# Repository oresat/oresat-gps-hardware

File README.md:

# oresat-gps-hardware 

## Overview

This is the repo for our OreSat GPS Card. For software, see the [oresat-gps-software](https://github.com/oresat/oresat-gps-software) repo.

The card has two GPS receivers on it:

* A [**SkyTraq Orion-B16** GNSS module](https://navspark.mybigcommerce.com/12mm-x-16mm-gnss-receiver-module-for-leo-applications/), a GNSS receiver module meant for university CubeSat use.
* An [Analog Devices MAX2771 SDR GNSS receiver IC](https://www.analog.com/en/products/max2771.html) that is read by the [Octavo OSD335x-SM processor's](https://octavosystems.com/octavo_products/osd335x-sm/) PRU and then parsed using the [GNSS-SDR project](https://gnss-sdr.org/) software.

## Status

TRL 6-7 ish. Flown, but not yet demonstrated to work in space.

* v1.1: Assembled, electrical and software test out, Orion not yet locked and demonstrated to work. MAX not yet tested.
* v1.0: Works: SkyTraq confirmed locked on ground. SDR datastream captured, and processed, but this software seems to be lost to the sands of time? Flown on OreSat0 but never turned on due to comms issues with OreSat0.

## License

All materials in this repo are copyright Portland State Aerospace Society and are licensed under the CERN Open Hardware Licence Version 2 -
Strongly Reciprocal (CERN-OHL-S v2), or any later version. A copy of the license is located in [here](LICENSE.md).

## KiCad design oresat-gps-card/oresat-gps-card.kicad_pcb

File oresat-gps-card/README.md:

---
title: "**OreSat GPS Card**"
subtitle: |
  **Fabrication and Assembly Information**\
  For build TIME-STAMP
fontsize: 10pt
geometry:
  - margin=0.5in
toc: true
toc-depth: 2
colorlinks: true
urlcolor: blue
---

\newpage

# About this Board

## Board Description

The OreSat GPS Card provides two GPS receivers for the OreSat bus:

1. The SkyTraq Orion B16 which is a COTS GPS receiver capable of lock while in orbit.
2. The MAX2769 SDR GPS receiver. This hardware is for a future SDR capability we'd
like to have, and might one day replace the much more expensive COTS receiver.

## Documentation Links

- GPS hardware Git repository: <https://github.com/oresat/oresat-gps-hardware>
- GPS software Git reposity: <https://github.com/oresat/oresat-gps-software>
- **TODO:** GPS Design Notes + Design Review Notes

## Documentation Files

| Filename                        | Notes                                    |
| ------------------------------- | ---------------------------------------- |
| README.pdf                      | This README file                         |
| PROJECT-NAME-outline.dxf        | Board outline (with holes) in DXF format |
| PROJECT-NAME-pcba.step          | 3D model of PCBA (with components)       |
| PROJECT-NAME-render-bot.jpg     | Render of the top of the 3D model        |
| PROJECT-NAME-render-bot.jpg     | Render of the bottom of the 3D model     |
| PROJECT-NAME-schematic.pdf      | PDF of board schematics                  |

## Contact Information

- Website: <https://www.oresat.org/>
- Email: <oresat@pdx.edu>
- Instagram: @pdxaerospace

## Board Renders

{width=50%}
{width=50%}

\newpage

# Printed Circuit Board (PCB) Fabrication Information

## Board Info

- 4 layer board
- Bounding box is 99.8 x 94.6 mm (3.93 x 3.72 in)
- Board thickness is 1.59 mm (0.063 inch)
- **Important:** See Materials and Stack Up sections below

## Board Requirements

- Design Rules
    - Minimum Trace / Space design rules
       - Outer layers: 0.127 mm (5.0 mil) / 0.127 mm (5.0 mil)
       - Inner layers: 0.127 mm (5.0 mil) / 0.127 mm (5.0 mil)
    - Outer dimension router tolerance: +/- 0.254 mm (10.0 mil)
    - Hole placement tolerance: +/- 0.075 mm (3.0 mil)
    - Inner tab routed slot tolerance: +/- 0.254 mm (10.0 mil)
- Drills
   - Drill Positional Tolerance: 0.051 mm (2.0 mil)
   - Drill Size tolerance: +/- 0.064 mm (2.5 mil)
- Plated/Un-plated holes
  - There are 6 un-plated (NPT) holes
  - There are 1477 plated through (PTH) holes
  - PTH minimum diameter: 0.254 mm (10 mil)
  - PTH minimum annulus: 0.102 mm (4 mil) radius
- Outline/Routing
  - Requires a 1.0 mm or smaller diameter routing bit
- Slots
  - There are no slots.
- Cutouts
  - There are no cutouts
- There are 3 fiducials on the top layer.
- Panel tabs ("mouse bites")
   - Card edges must be smooth; no mouse bites or other intrusions into the card outline.
   - If external mouse bites are required, minimize and customer will remove by hand before assembly.
- If not otherwise specified, build to IPC 6012 Class 2 or better.

## Materials

- Controlled impedance
   - The stackup is critical for the performance of high speed signals on this board.
   - As long as the stackup is controlled, the board is not considered controlled impedance.
- Isola FR408HR or material with equivalent Dk.
- Board Surface treatment should be ENIG, althogh immersion Silver is acceptable.
- White silkscreen on top and bottom surface
- Taiyo PSR-4000 or equivalent soldermask on top and bottom, no requirements for color.

## Stack Up

| Layer         | Thickness           | Notes                                        |
|---------------|---------------------|----------------------------------------------|
| Top Copper    | 0.043 mm /  1.7 mil |  Layer 1 foil, 1 oz Cu after plating         |
| prepreg       | 0.200 mm /  7.9 mil |  Prepreg - Isola FR408HR 2113                |
| Layer 2       | 0.018 mm /  0.7 mil |  Layer 2 foil, 0.5 oz Cu                     |
| Core          | 0.991 mm /   39 mil |  Core Isola FR408HR                          |
| Layer 3       | 0.018 mm /  0.7 mil |  Layer 3 foil, 0.5 oz Cu                     |
| prepreg       | 0.200 mm /  7.9 mil |  Prepreg - Isola FR408HR 2113                |
| Bottom Copper | 0.043 mm /  1.7 mil |  Layer 4 foil, 1 oz copper after plating     |
| **Total Stackup** | **1.588 mm / 62.5 mil** |                                      |

## Array / Panel Information

- Coordinate with Contract Manufacturer (CM) for optimal size of this panel.
- If no feedback from CM, then produce single boards (no panel).

## Fabrication Files

### IPC-2581 File

| Filename                 | Notes                                   |
| ------------------------ | --------------------------------------- |
| PROJECT-NAME-ipc2581.xml | IPC-2581 board information file         |

### Legacy PCB Files

| Filename                      | Notes                                         |
| ------------------------------| --------------------------------------------- |
| PROJECT-NAME-Edge_Cuts.gbr    | RS274X file for the dimension (outline) layer |
| PROJECT-NAME-F_Silkscreen.gbr | RS274X file for the top silkscreen            |
| PROJECT-NAME-F_Mask.gbr       | RS274X file for the top soldermask            |
| PROJECT-NAME-F_Cu.gbr         | RS274X file for the top copper layer          |
| PROJECT-NAME-In1_Cu.gbr       | RS274X file for the layer 2 copper            |
| PROJECT-NAME-In2_Cu.gbr       | RS274X file for the layer 3 copper            |
| PROJECT-NAME-B_Cu.gbr         | RS274X file for the bottom copper layer       |
| PROJECT-NAME-B_Mask.gbr       | RS274X file for the bottom soldermask         |
| PROJECT-NAME-B_Silkscreen.gbr | RS274X file for the bottom silkscreen         |
| PROJECT-NAME-NPTH.drl         | Excellon file for non-plated through holes    |
| PROJECT-NAME-PTH.drl          | Excellon file for plated through holes        | 

\newpage

# Printed Circuit Board Assembly (PCBA) Information

## Assembly Info

- All components are on the top side of the board.
- This PCBA is mostly surface mount (SMT) with a few (THT) components.

## Assembly Requirements

- Assemble to IPC Class 2 or better
- Bake components that are not moisture sealed to appropriate levels as required.
- Solder paste MUST be leaded.
- Aqueous flux and wash strongly preferred.
   - Clean to NASA Standard "Visibly Clean (VC)": No particles or residues are visible to the naked eye.
- No conformal coating.
- Ship in antistatic protective bag

## Component Specific Assembly Information

- SMPM connectors (CM1) should be hand-added (there is no solder paste for their footprints) according to the OreSat SMPM SOP.
- U23 is extremely expensive ($400 ea).

## Assembly Files

### IPC-2581 File

| Filename                 | Notes                           |
| ------------------------ | ------------------------------- |
| PROJECT-NAME-ipc2581.xml | IPC-2581 board information file |

### Bill of Materials (BOM)

| Filename             | Description                            |
| -------------------- | -------------------------------------- |
| PROJECT-NAME-bom.csv | BOM in Comma Separated Variable format |

### Solder Paste Stencils

| Filename                 | Notes                                            |
| ------------------------ | ------------------------------------------------ |
| PROJECT-NAME-B_Paste.gbr | RS274X file for top/front solder paste stencil   |
| PROJECT-NAME-F_Paste.gbr | RS274X file for bottom/back solder paste stencil |

### Mounting/Placement Location

| Filename            | Description                                 |
| ------------------- | ------------------------------------------- |
| PROJECT-NAME-3u.pos | Pick and place locations for components     |

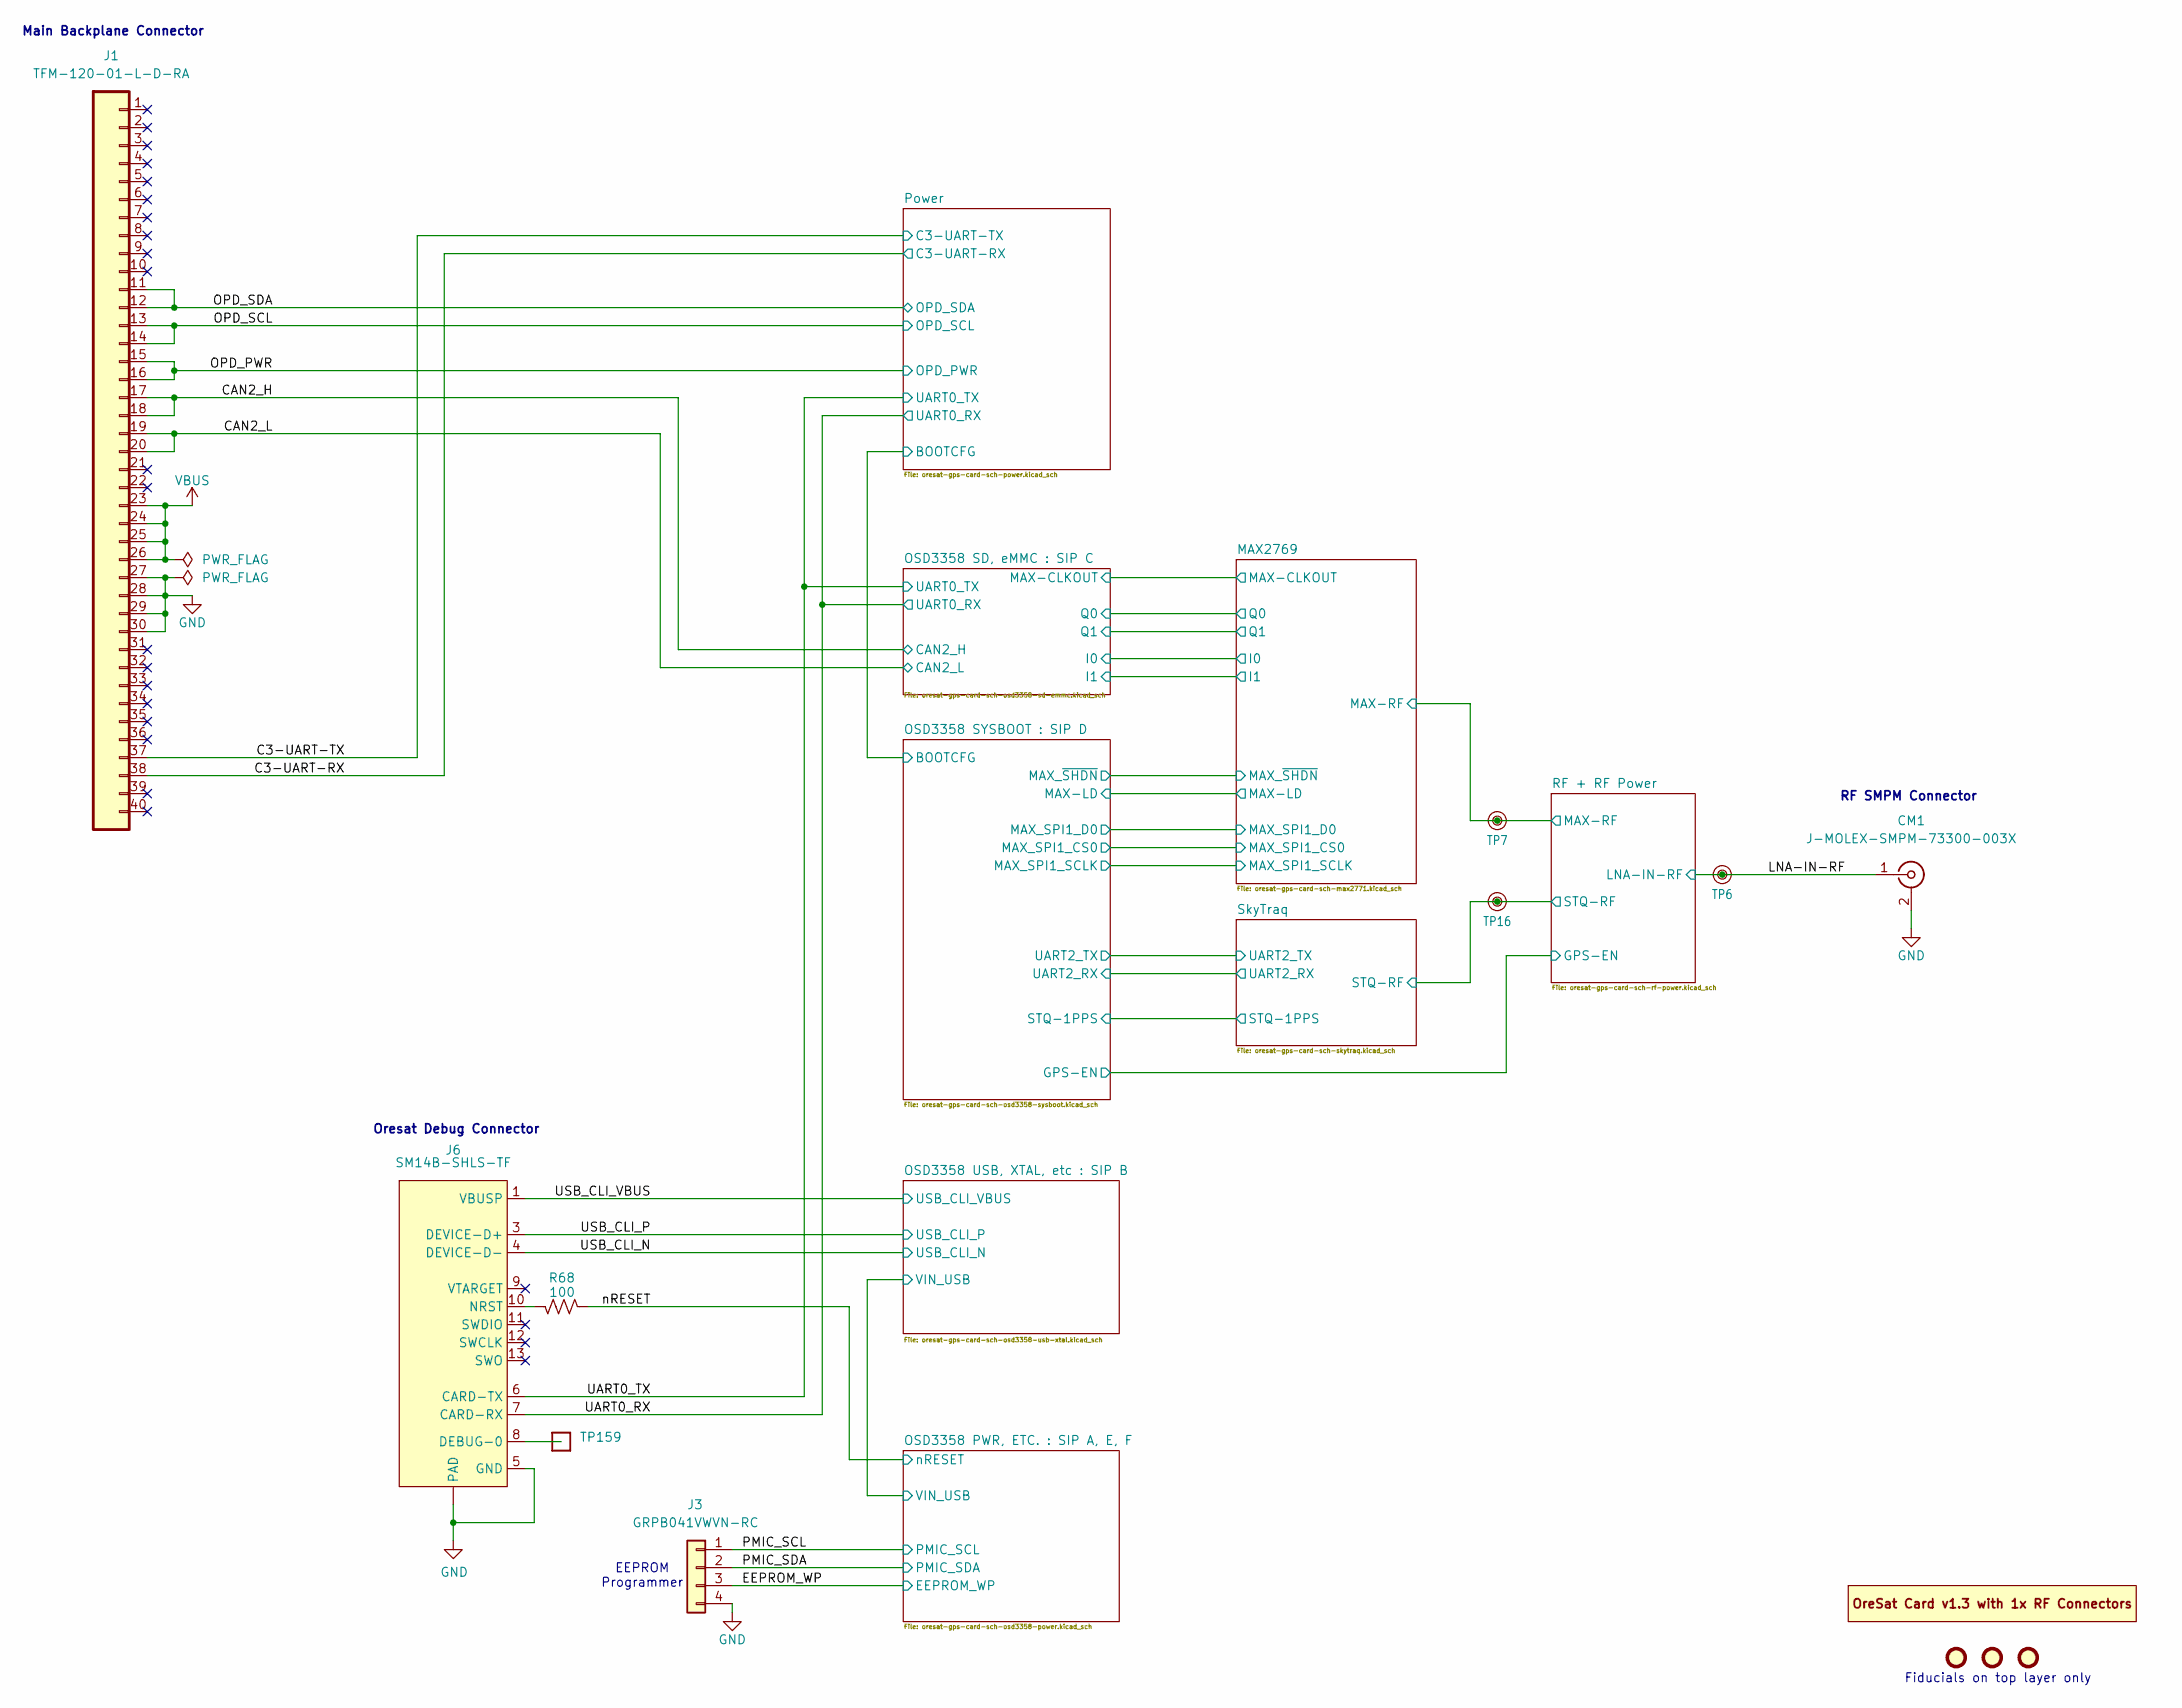
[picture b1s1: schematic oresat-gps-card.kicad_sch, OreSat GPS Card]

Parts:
CM1: J-MOLEX-SMPM-73300-003X; J-MOLEX-SMPM-073300-002X; MPN 2477330-1
FID1, FID2, FID3: Fiducial; Fiducial_1mm_Mask2mm
J1: TFM-120-01-L-D-RA; J-SAMTEC-TFM-120-X1-XXX-D-RA; MPN TFM-120-01-L-D-RA
J3: GRPB041VWVN-RC; PinHeader_1x04_P1.27mm_Vertical; MPN GRPB041VWVN-RC
J6: SM14B-SHLS-TF; J-JST-SM14BSHLSTF; MPN SM14B-SHLS-TF
PCB1: ORESAT-CARD-V1.3-GENERIC-1RF-POS2; ORESAT-CARD-V1.3-1RF-POS2
R68: 100; 0603-C-NOSILK; MPN RMCF0603FT100R
TP6, TP7, TP16: TestPoint_RF_Probe
TP159: Test-Point; TestPoint-0.75mm-th

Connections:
/C3-UART-RX: J1.38; also elsewhere on the board
/C3-UART-TX: J1.37; also elsewhere on the board
/CAN2_H: J1.17, J1.18; also elsewhere on the board
/CAN2_L: J1.19, J1.20; also elsewhere on the board
/EEPROM_WP: J3.3; also elsewhere on the board
/LNA-IN-RF: CM1.1 (In), TP6.1 (1_1); also elsewhere on the board
/MAX2769/MAX-RF: TP7.1 (1_1); also elsewhere on the board
/OPD_PWR: J1.15, J1.16; also elsewhere on the board
/OPD_SCL: J1.13, J1.14; also elsewhere on the board
/OPD_SDA: J1.11, J1.12; also elsewhere on the board
/PMIC_SCL: J3.1; also elsewhere on the board
/PMIC_SDA: J3.2; also elsewhere on the board
/RF + RF Power/STQ-RF: TP16.1 (1_1); also elsewhere on the board
/UART0_RX: J6.7 (CARD-RX); also elsewhere on the board
/UART0_TX: J6.6 (CARD-TX); also elsewhere on the board
/USB_CLI_N: J6.4 (DEVICE-D-); also elsewhere on the board
/USB_CLI_P: J6.3 (DEVICE-D+); also elsewhere on the board
/USB_CLI_VBUS: J6.1 (VBUSP), J6.2 (VBUSP); also elsewhere on the board
/nRESET: R68.2; also elsewhere on the board
GND: CM1.2 (Ext), J1.27, J1.28, J1.29, J1.30, J3.4, J6.5 (GND), J6.14 (GND), J6.15 (PAD), J6.16 (PAD); also elsewhere on the board
unnamed: J6.8 (DEBUG-0), TP159.1 (1_1)
unnamed: J6.10 (NRST), R68.1
VBUS: J1.23, J1.24, J1.25, J1.26; also elsewhere on the board

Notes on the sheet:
RF SMPM Connector
Main Backplane Connector
Oresat Debug Connector
EEPROM Programmer
Fiducials on top layer only

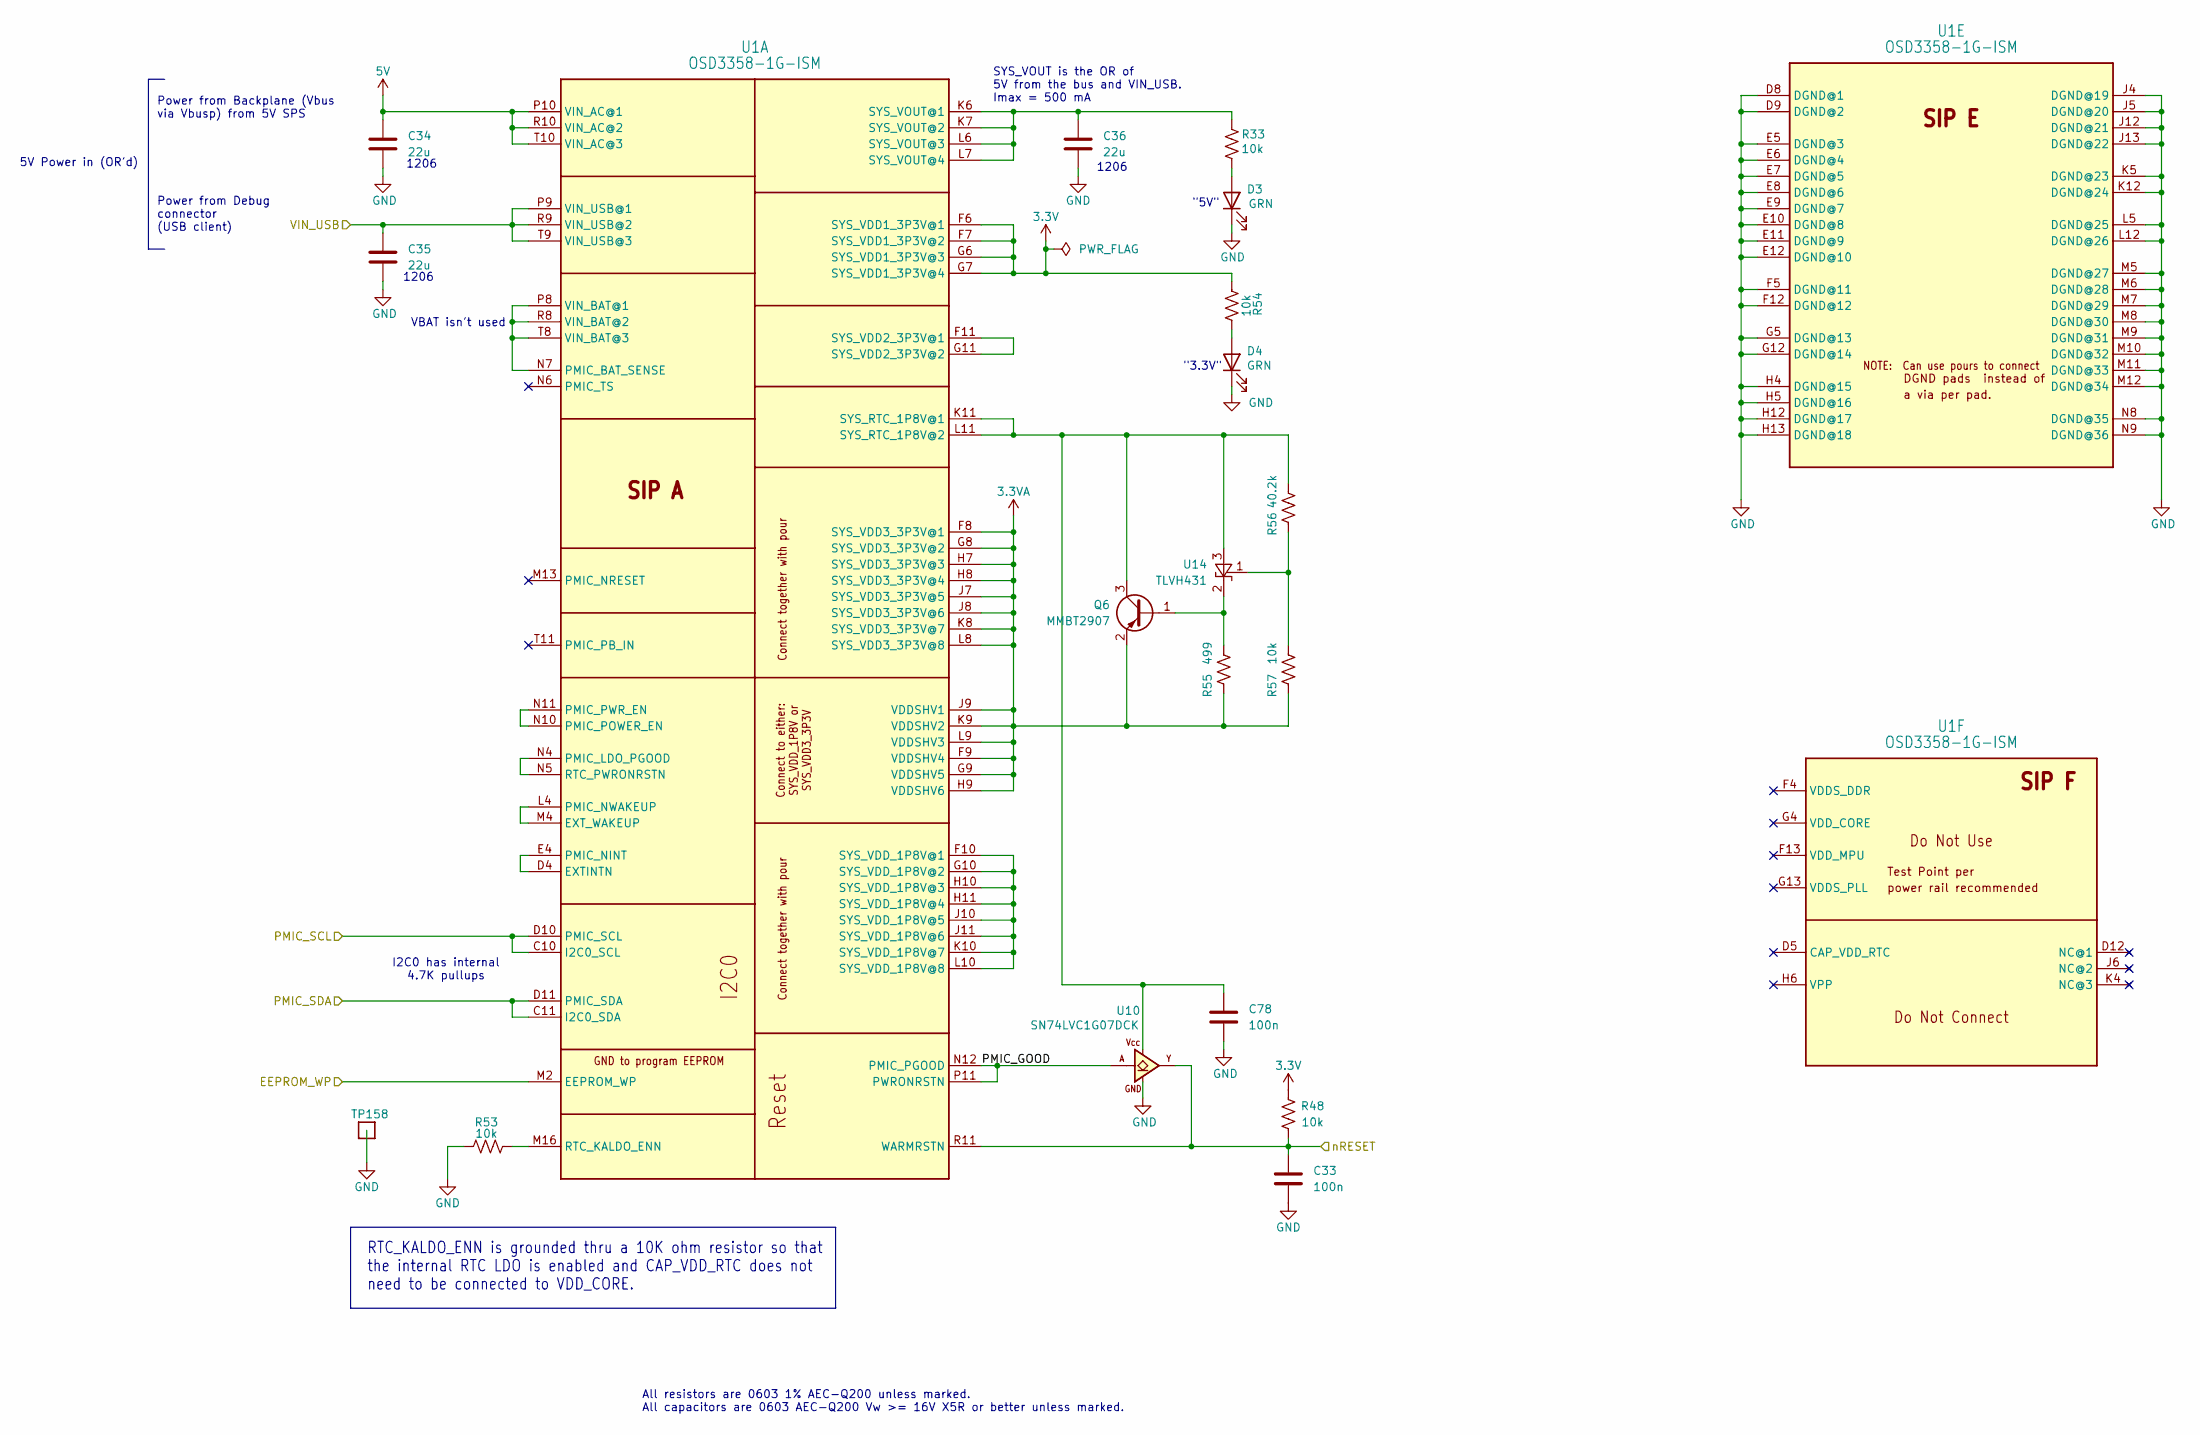
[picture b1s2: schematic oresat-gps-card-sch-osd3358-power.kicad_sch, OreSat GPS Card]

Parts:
C33, C78: 100n; 0603-C-NOSILK; MPN C0603C104K5RACAUTO
C34, C35, C36: 22u; C_1206_3216Metric; MPN GRT31CC81C226KE01L
D3, D4: GRN; LED_0603_1608Metric; MPN 150060GS75000
Q6: MMBT2907; SOT23; MPN PMBT2907,215
R33, R48, R53, R54, R57: 10k; 0603-C-NOSILK; MPN RMCF0603FT10K0
R55: 499; 0603-C-NOSILK; MPN RMCF0603FT499R
R56: 40.2k; 0603-C-NOSILK; MPN RMCF0603FT40K2
TP158: Test-Point; TestPoint-0.75mm-th
U1: OSD3358-1G-ISM; U-Octavo-OSD335X-BGA-256; MPN OSD3358-1G-ISM
U10: SN74LVC1G07DCK; SOT-353_SC-70-5; MPN SN74LVC1G07DCKR
U14: TLVH431; SOT-23; MPN TLVH431AQDBZR

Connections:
3.3V: R48.2, R54.1, U1.F6 (SYS_VDD1_3P3V@1), U1.F7 (SYS_VDD1_3P3V@2), U1.G6 (SYS_VDD1_3P3V@3), U1.G7 (SYS_VDD1_3P3V@4); also elsewhere on the board
3.3VA: Q6.2 (E), R55.1, R57.1, U1.F8 (SYS_VDD3_3P3V@1), U1.F9 (VDDSHV4), U1.G8 (SYS_VDD3_3P3V@2), U1.G9 (VDDSHV5), U1.H7 (SYS_VDD3_3P3V@3), U1.H8 (SYS_VDD3_3P3V@4), U1.H9 (VDDSHV6), U1.J7 (SYS_VDD3_3P3V@5), U1.J8 (SYS_VDD3_3P3V@6), U1.J9 (VDDSHV1), U1.K8 (SYS_VDD3_3P3V@7), U1.K9 (VDDSHV2), U1.L8 (SYS_VDD3_3P3V@8), U1.L9 (VDDSHV3)
5V: C34.1, U1.P10 (VIN_AC@1), U1.R10 (VIN_AC@2), U1.T10 (VIN_AC@3); also elsewhere on the board
/EEPROM_WP: U1.M2 (EEPROM_WP); also elsewhere on the board
/OSD3358 PWR, ETC. : SIP A, E, F/PMIC_GOOD: U1.N12 (PMIC_PGOOD), U1.P11 (PWRONRSTN), U10.2 (A)
/OSD3358 PWR, ETC. : SIP A, E, F/VIN_USB: C35.1, U1.P9 (VIN_USB@1), U1.R9 (VIN_USB@2), U1.T9 (VIN_USB@3); also elsewhere on the board
/PMIC_SCL: U1.C10 (I2C0_SCL), U1.D10 (PMIC_SCL); also elsewhere on the board
/PMIC_SDA: U1.C11 (I2C0_SDA), U1.D11 (PMIC_SDA); also elsewhere on the board
/nRESET: C33.1, R48.1, U1.R11 (WARMRSTN), U10.4 (Y); also elsewhere on the board
GND: C33.2, C34.2, C35.2, C36.2, C78.2, D3.1 (K), D4.1 (K), R53.1, TP158.1 (1_1), U1.D8 (DGND@1), U1.D9 (DGND@2), U1.E5 (DGND@3), U1.E6 (DGND@4), U1.E7 (DGND@5), U1.E8 (DGND@6), U1.E9 (DGND@7), U1.E10 (DGND@8), U1.E11 (DGND@9), U1.E12 (DGND@10), U1.F5 (DGND@11), U1.F12 (DGND@12), U1.G5 (DGND@13), U1.G12 (DGND@14), U1.H4 (DGND@15), U1.H5 (DGND@16), U1.H12 (DGND@17), U1.H13 (DGND@18), U1.J4 (DGND@19), U1.J5 (DGND@20), U1.J12 (DGND@21), U1.J13 (DGND@22), U1.K5 (DGND@23), U1.K12 (DGND@24), U1.L5 (DGND@25), U1.L12 (DGND@26), U1.M5 (DGND@27), U1.M6 (DGND@28), U1.M7 (DGND@29), U1.M8 (DGND@30), U1.M9 (DGND@31), U1.M10 (DGND@32), U1.M11 (DGND@33), U1.M12 (DGND@34), U1.N8 (DGND@35), U1.N9 (DGND@36), U10.3 (GND); also elsewhere on the board
unnamed: D3.2 (A), R33.1
unnamed: D4.2 (A), R54.2
unnamed: Q6.1 (B), R55.2, U14.2 (K)
unnamed: C78.1, Q6.3 (C), R56.2, U1.K11 (SYS_RTC_1P8V@1), U1.L11 (SYS_RTC_1P8V@2), U10.5 (VCC), U14.3 (A)
unnamed: U1.D4 (EXTINTN), U1.E4 (PMIC_NINT)
unnamed: U1.L4 (PMIC_NWAKEUP), U1.M4 (EXT_WAKEUP)
unnamed: U1.N7 (PMIC_BAT_SENSE), U1.P8 (VIN_BAT@1), U1.R8 (VIN_BAT@2), U1.T8 (VIN_BAT@3)
unnamed: U1.N4 (PMIC_LDO_PGOOD), U1.N5 (RTC_PWRONRSTN)
unnamed: U1.N10 (PMIC_POWER_EN), U1.N11 (PMIC_PWR_EN)
unnamed: R53.2, U1.M16 (RTC_KALDO_ENN)
unnamed: U1.F11 (SYS_VDD2_3P3V@1), U1.G11 (SYS_VDD2_3P3V@2)
unnamed: U1.F10 (SYS_VDD_1P8V@1), U1.G10 (SYS_VDD_1P8V@2), U1.H10 (SYS_VDD_1P8V@3), U1.H11 (SYS_VDD_1P8V@4), U1.J10 (SYS_VDD_1P8V@5), U1.J11 (SYS_VDD_1P8V@6), U1.K10 (SYS_VDD_1P8V@7), U1.L10 (SYS_VDD_1P8V@8)
unnamed: C36.1, R33.2, U1.K6 (SYS_VOUT@1), U1.K7 (SYS_VOUT@2), U1.L6 (SYS_VOUT@3), U1.L7 (SYS_VOUT@4)
unnamed: R56.1, R57.2, U14.1 (REF)

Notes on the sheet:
Power from Debug connector (USB client)
"3.3V"
5V Power in (OR'd)
1206
I2C0 has internal 4.7K pullups
SYS_VOUT is the OR of 5V from the bus and VIN_USB. Imax = 500 mA
All resistors are 0603 1% AEC-Q200 unless marked. All capacitors are 0603 AEC-Q200 Vw >= 16V X5R or better unless marked.
VBAT isn't used
"5V"
RTC_KALDO_ENN is grounded thru a 10K ohm resistor so that the internal RTC LDO is enabled and CAP_VDD_RTC does not need to be connected to VDD_CORE.
Power from Backplane (Vbus via Vbusp) from 5V SPS

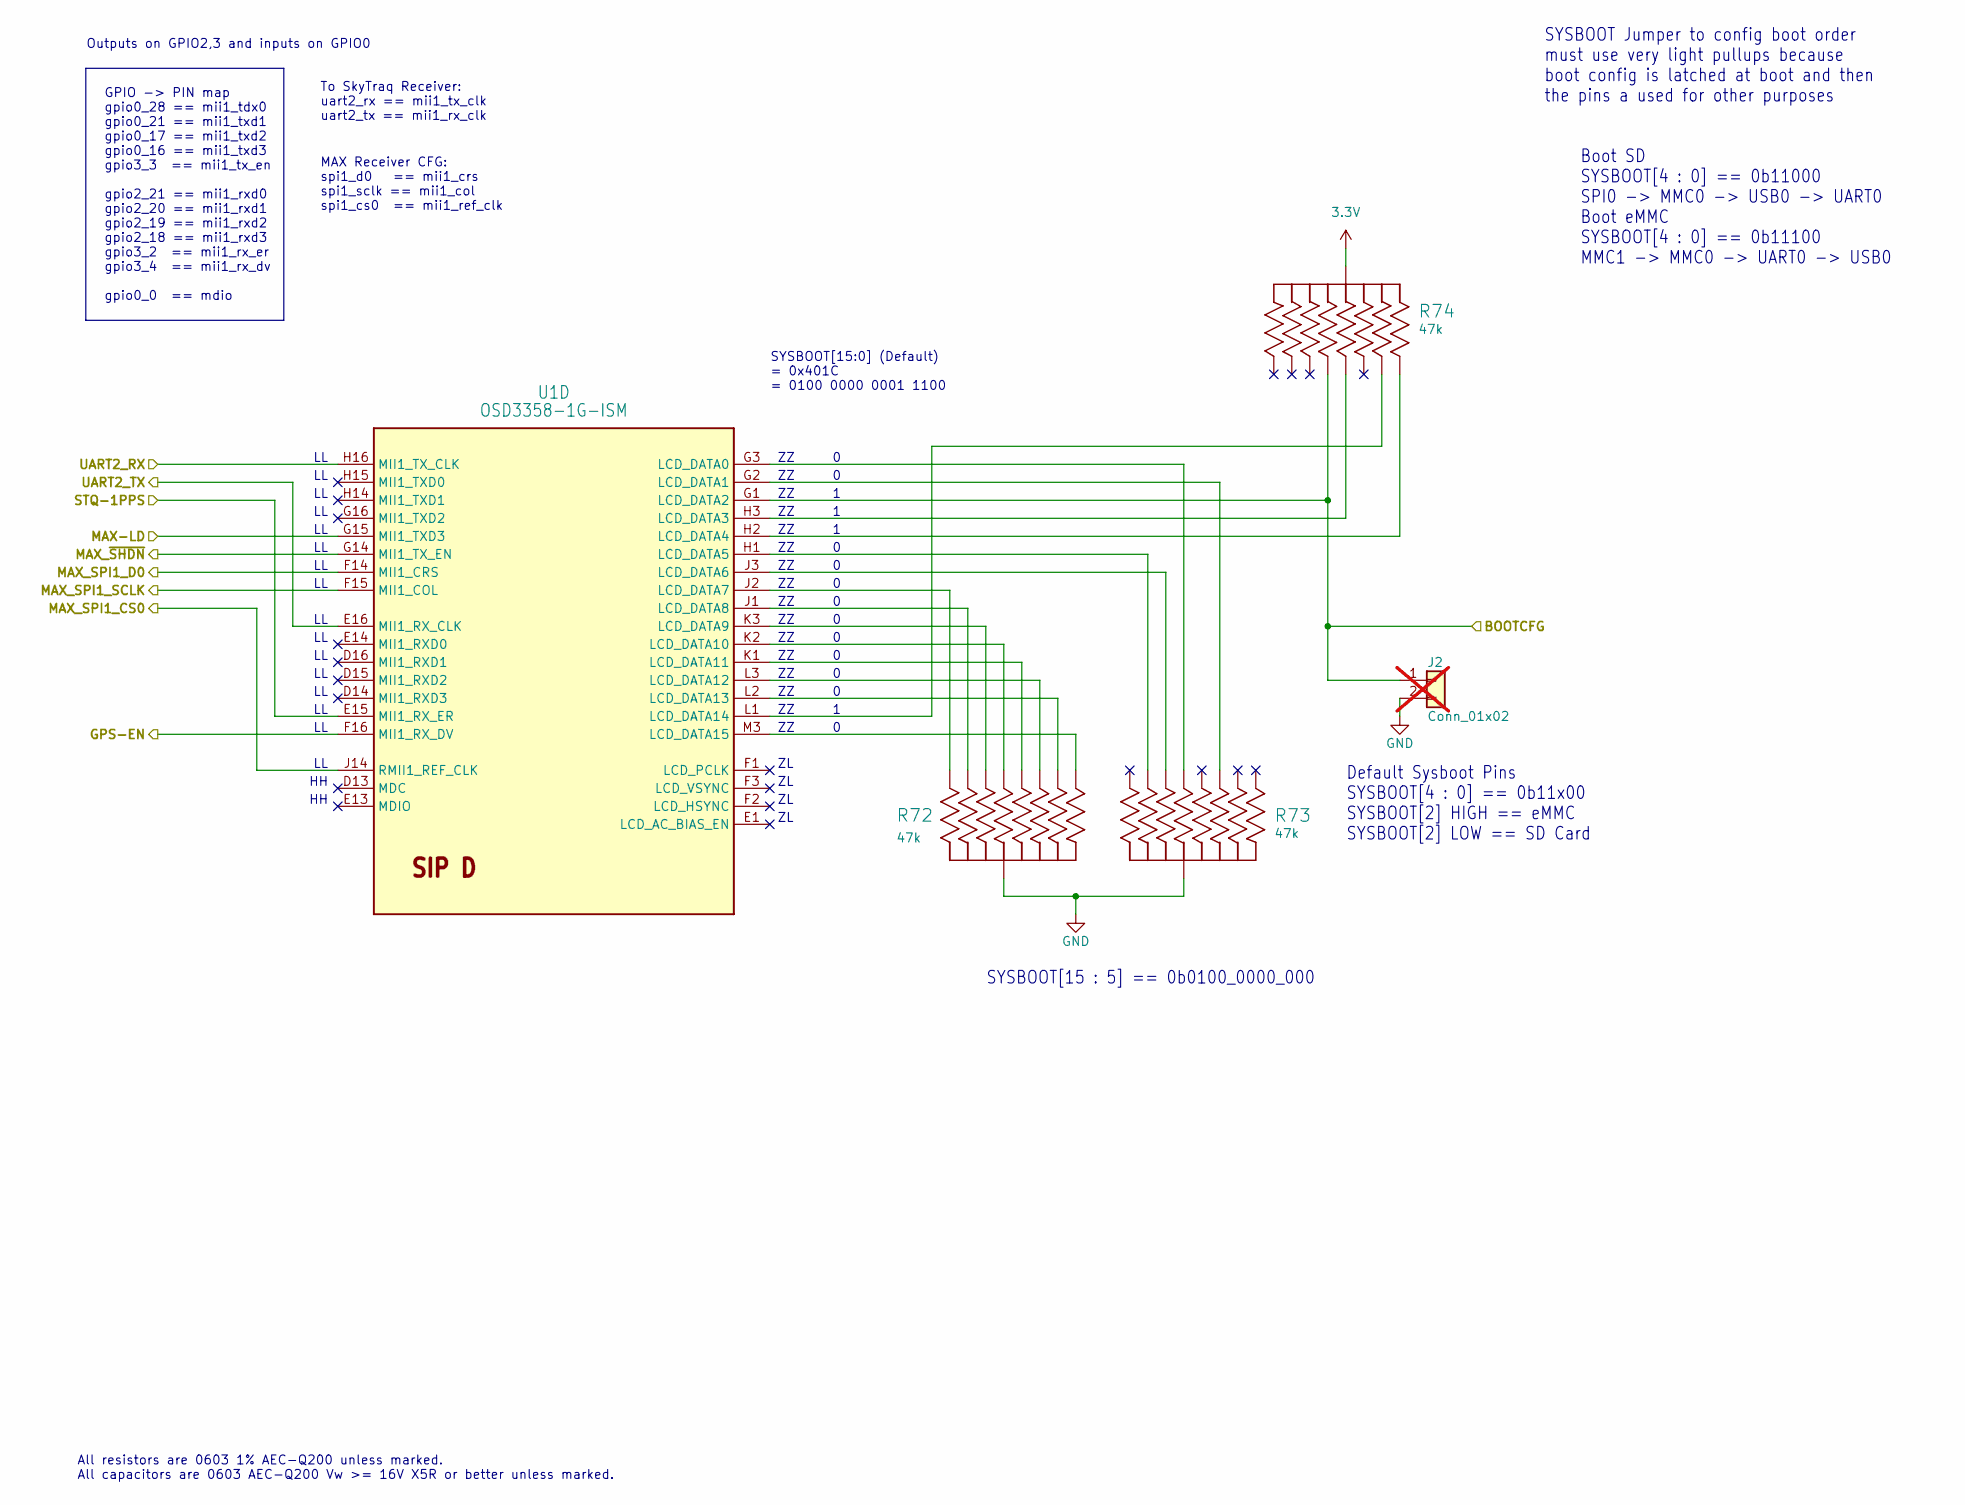
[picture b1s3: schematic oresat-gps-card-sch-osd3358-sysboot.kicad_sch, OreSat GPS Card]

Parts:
J2: Conn_01x02; PinHeader_1x02_P2.54mm_Vertical; not fitted
R72, R73, R74: 47k; Panasonic_Resistor_Array_EXBA10; MPN EXB-A10P473J
U1: OSD3358-1G-ISM; U-Octavo-OSD335X-BGA-256; MPN OSD3358-1G-ISM

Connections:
3.3V: R74.5 (55), R74.10 (55); also elsewhere on the board
/MAX2769/MAX-LD: U1.G15 (MII1_TXD3); also elsewhere on the board
/MAX2769/MAX_SPI1_CS0: U1.J14 (RMII1_REF_CLK); also elsewhere on the board
/MAX2769/MAX_SPI1_D0: U1.F14 (MII1_CRS); also elsewhere on the board
/MAX2769/MAX_SPI1_SCLK: U1.F15 (MII1_COL); also elsewhere on the board
/MAX2769/MAX_~SHDN: U1.G14 (MII1_TX_EN); also elsewhere on the board
/OSD3358 SYSBOOT : SIP D/BOOTCFG: J2.1, R74.8 (88), U1.G1 (LCD_DATA2); also elsewhere on the board
/OSD3358 SYSBOOT : SIP D/GPS-EN: U1.F16 (MII1_RX_DV); also elsewhere on the board
/OSD3358 SYSBOOT : SIP D/STQ-1PPS: U1.E15 (MII1_RX_ER); also elsewhere on the board
/OSD3358 SYSBOOT : SIP D/UART2_RX: U1.H16 (MII1_TX_CLK); also elsewhere on the board
/OSD3358 SYSBOOT : SIP D/UART2_TX: U1.E16 (MII1_RX_CLK); also elsewhere on the board
GND: J2.2, R72.5 (55), R72.10 (55), R73.5 (55), R73.10 (55); also elsewhere on the board
unnamed: R72.1 (11), U1.M3 (LCD_DATA15)
unnamed: R72.2 (22), U1.L3 (LCD_DATA12)
unnamed: R72.3 (33), U1.K2 (LCD_DATA10)
unnamed: R72.4 (44), U1.J1 (LCD_DATA8)
unnamed: R72.6 (66), U1.J2 (LCD_DATA7)
unnamed: R72.7 (77), U1.K3 (LCD_DATA9)
unnamed: R72.8 (88), U1.K1 (LCD_DATA11)
unnamed: R72.9 (99), U1.L2 (LCD_DATA13)
unnamed: R73.2 (22), U1.G2 (LCD_DATA1)
unnamed: R73.3 (33), U1.G3 (LCD_DATA0)
unnamed: R73.4 (44), U1.H1 (LCD_DATA5)
unnamed: R73.7 (77), U1.J3 (LCD_DATA6)
unnamed: R74.3 (33), U1.H3 (LCD_DATA3)
unnamed: R74.4 (44), U1.L1 (LCD_DATA14)
unnamed: R74.6 (66), U1.H2 (LCD_DATA4)

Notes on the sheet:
All resistors are 0603 1% AEC-Q200 unless marked. All capacitors are 0603 AEC-Q200 Vw >= 16V X5R or better unless marked.
Default Sysboot Pins SYSBOOT[4 : 0] == 0b11x00 SYSBOOT[2] HIGH == eMMC SYSBOOT[2] LOW == SD Card
Outputs on GPIO2,3 and inputs on GPIO0
Boot SD SYSBOOT[4 : 0] == 0b11000 SPI0 -> MMC0 -> USB0 -> UART0 Boot eMMC SYSBOOT[4 : 0] == 0b11100 MMC1 -> MMC0 -> UART0 -> USB0
To SkyTraq Receiver: uart2_rx == mii1_tx_clk uart2_tx == mii1_rx_clk
SYSBOOT Jumper to config boot order must use very light pullups because boot config is latched at boot and then the pins a used for other purposes
MAX Receiver CFG: spi1_d0 == mii1_crs spi1_sclk == mii1_col spi1_cs0 == mii1_ref_clk
SYSBOOT[15:0] (Default) = 0x401C = 0100 0000 0001 1100
SYSBOOT[15 : 5] == 0b0100_0000_000
GPIO -> PIN map gpio0_28 == mii1_tdx0 gpio0_21 == mii1_txd1 gpio0_17 == mii1_txd2 gpio0_16 == mii1_txd3 gpio3_3 == mii1_tx_en gpio2_21 == mii1_rxd0 gpio2_20 == mii1_rxd1 gpio2_19 == mii1_rxd2 gpio2_18 == mii1_rxd3 gpio3_2 == mii1_rx_er gpio3_4 == mii1_rx_dv gpio0_0 == mdio

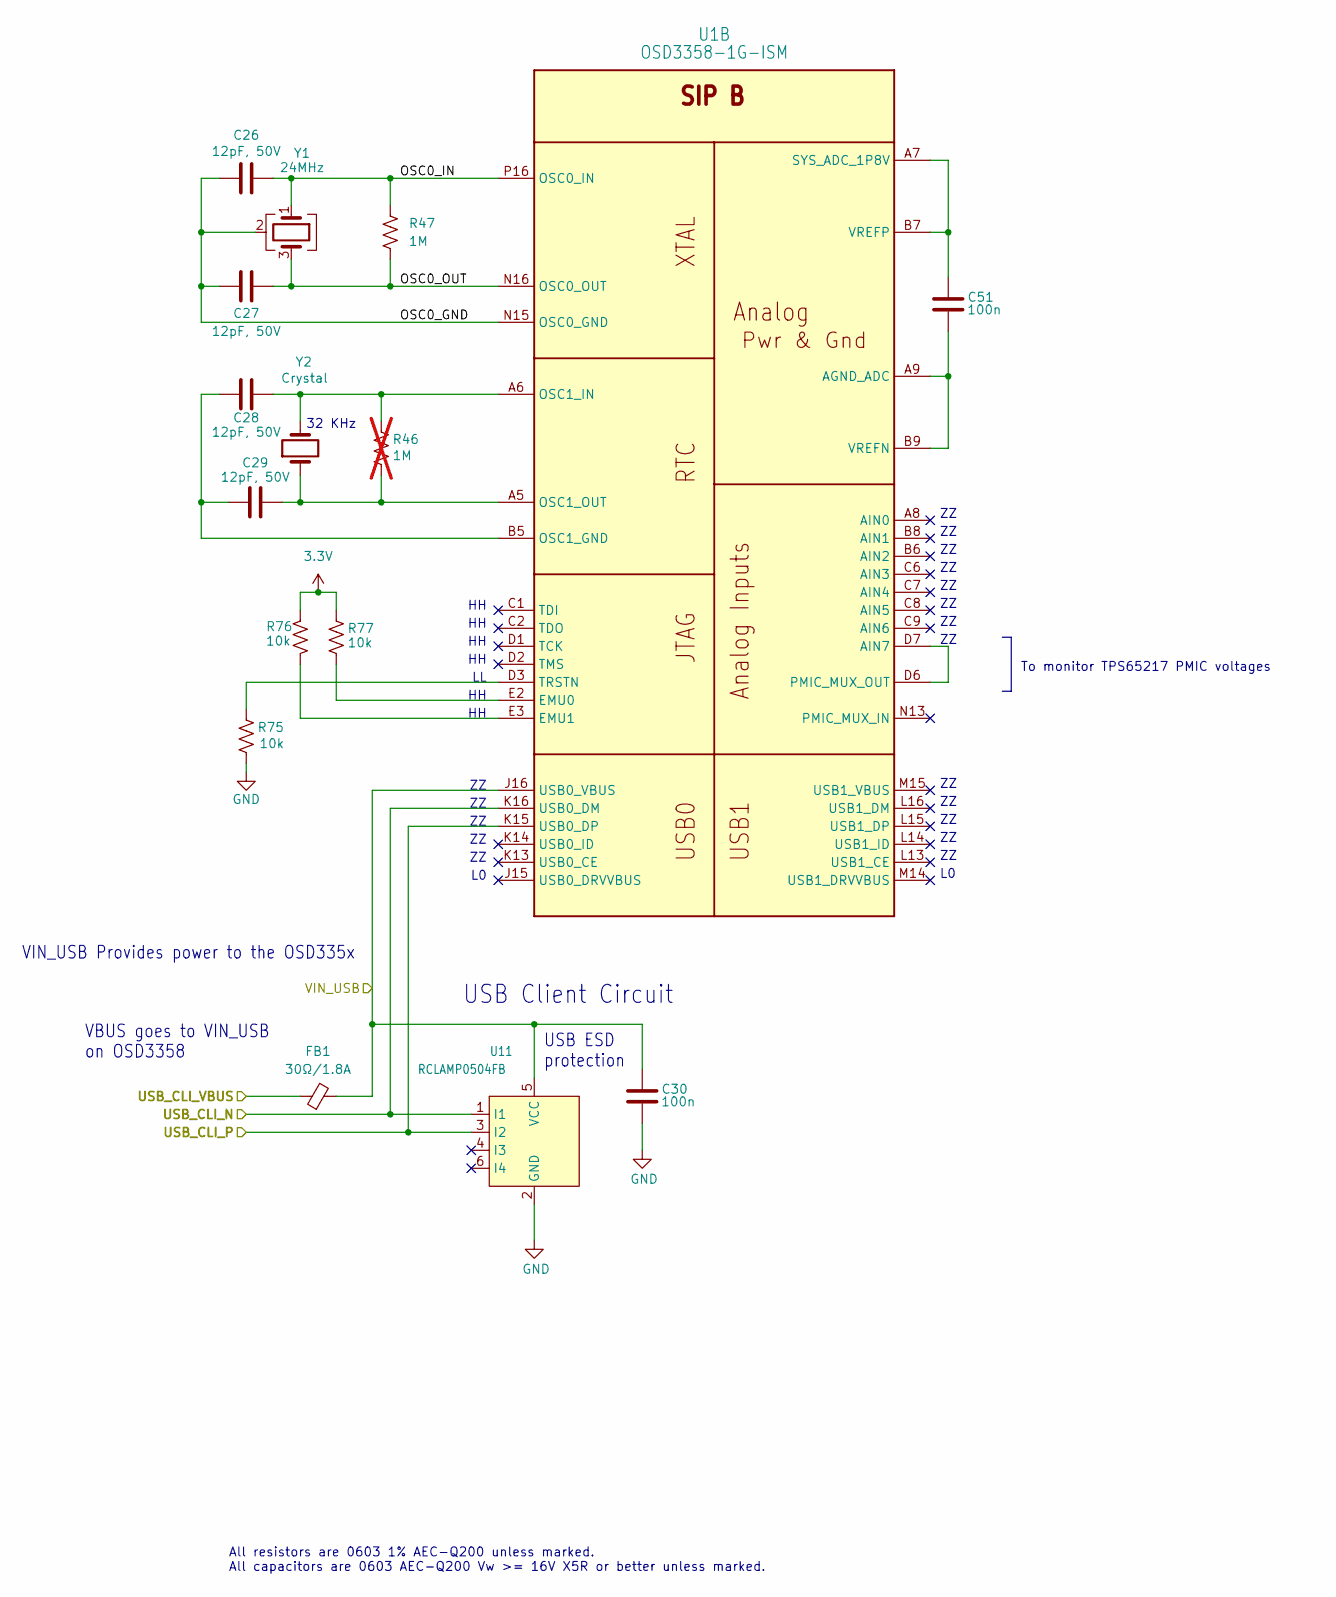
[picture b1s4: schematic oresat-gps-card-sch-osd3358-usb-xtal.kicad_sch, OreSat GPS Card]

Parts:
C26, C27, C28, C29: 12pF, 50V; 0603-C-NOSILK; MPN GRM1885C1H120JA01D
C30, C51: 100n; 0603-C-NOSILK; MPN C0603C104K5RACAUTO
FB1: 30Ω/1.8A; L_0603_1608Metric; MPN BLM18KG300JH1D
R46: 1M; R_0603_1608Metric; not fitted
R47: 1M; 0603-C-NOSILK; MPN RMCF0603FT1M00
R75, R76, R77: 10k; 0603-C-NOSILK; MPN RMCF0603FT10K0
U1: OSD3358-1G-ISM; U-Octavo-OSD335X-BGA-256; MPN OSD3358-1G-ISM
U11: RCLAMP0504FB; SOT-363_SC-70-6; MPN RCLAMP0504FBTCT
Y1: 24MHz; CRYSTAL-5X3.2-4SMD; MPN ECS-240-12-30BQ-AEN-TR
Y2: Crystal; CRYSTAL_3.2X1.5; MPN ABS07-32.768KHZ-T

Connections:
3.3V: R76.1, R77.1; also elsewhere on the board
/OSD3358 PWR, ETC. : SIP A, E, F/VIN_USB: C30.2, FB1.2, U1.J16 (USB0_VBUS), U11.5 (VCC); also elsewhere on the board
/OSD3358 USB, XTAL, etc : SIP B/OSC0_GND: C26.1, C27.1, U1.N15 (OSC0_GND), Y1.2 (G), Y1.4 (G)
/OSD3358 USB, XTAL, etc : SIP B/OSC0_IN: C26.2, R47.1, U1.P16 (OSC0_IN), Y1.1
/OSD3358 USB, XTAL, etc : SIP B/OSC0_OUT: C27.2, R47.2, U1.N16 (OSC0_OUT), Y1.3
/USB_CLI_N: U1.K16 (USB0_DM), U11.1 (I1); also elsewhere on the board
/USB_CLI_P: U1.K15 (USB0_DP), U11.3 (I2); also elsewhere on the board
/USB_CLI_VBUS: FB1.1; also elsewhere on the board
GND: C30.1, R75.2, U11.2 (GND); also elsewhere on the board
unnamed: C51.1, U1.A9 (AGND_ADC), U1.B9 (VREFN)
unnamed: U1.D6 (PMIC_MUX_OUT), U1.D7 (AIN7)
unnamed: R77.2, U1.E2 (EMU0)
unnamed: R76.2, U1.E3 (EMU1)
unnamed: C28.1, C29.1, U1.B5 (OSC1_GND)
unnamed: C28.2, R46.1, U1.A6 (OSC1_IN), Y2.2
unnamed: C29.2, R46.2, U1.A5 (OSC1_OUT), Y2.1
unnamed: C51.2, U1.A7 (SYS_ADC_1P8V), U1.B7 (VREFP)
unnamed: R75.1, U1.D3 (TRSTN)

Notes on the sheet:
To monitor TPS65217 PMIC voltages
VBUS goes to VIN_USB on OSD3358
VIN_USB Provides power to the OSD335x
USB Client Circuit
32 KHz
USB ESD protection
All resistors are 0603 1% AEC-Q200 unless marked. All capacitors are 0603 AEC-Q200 Vw >= 16V X5R or better unless marked.
